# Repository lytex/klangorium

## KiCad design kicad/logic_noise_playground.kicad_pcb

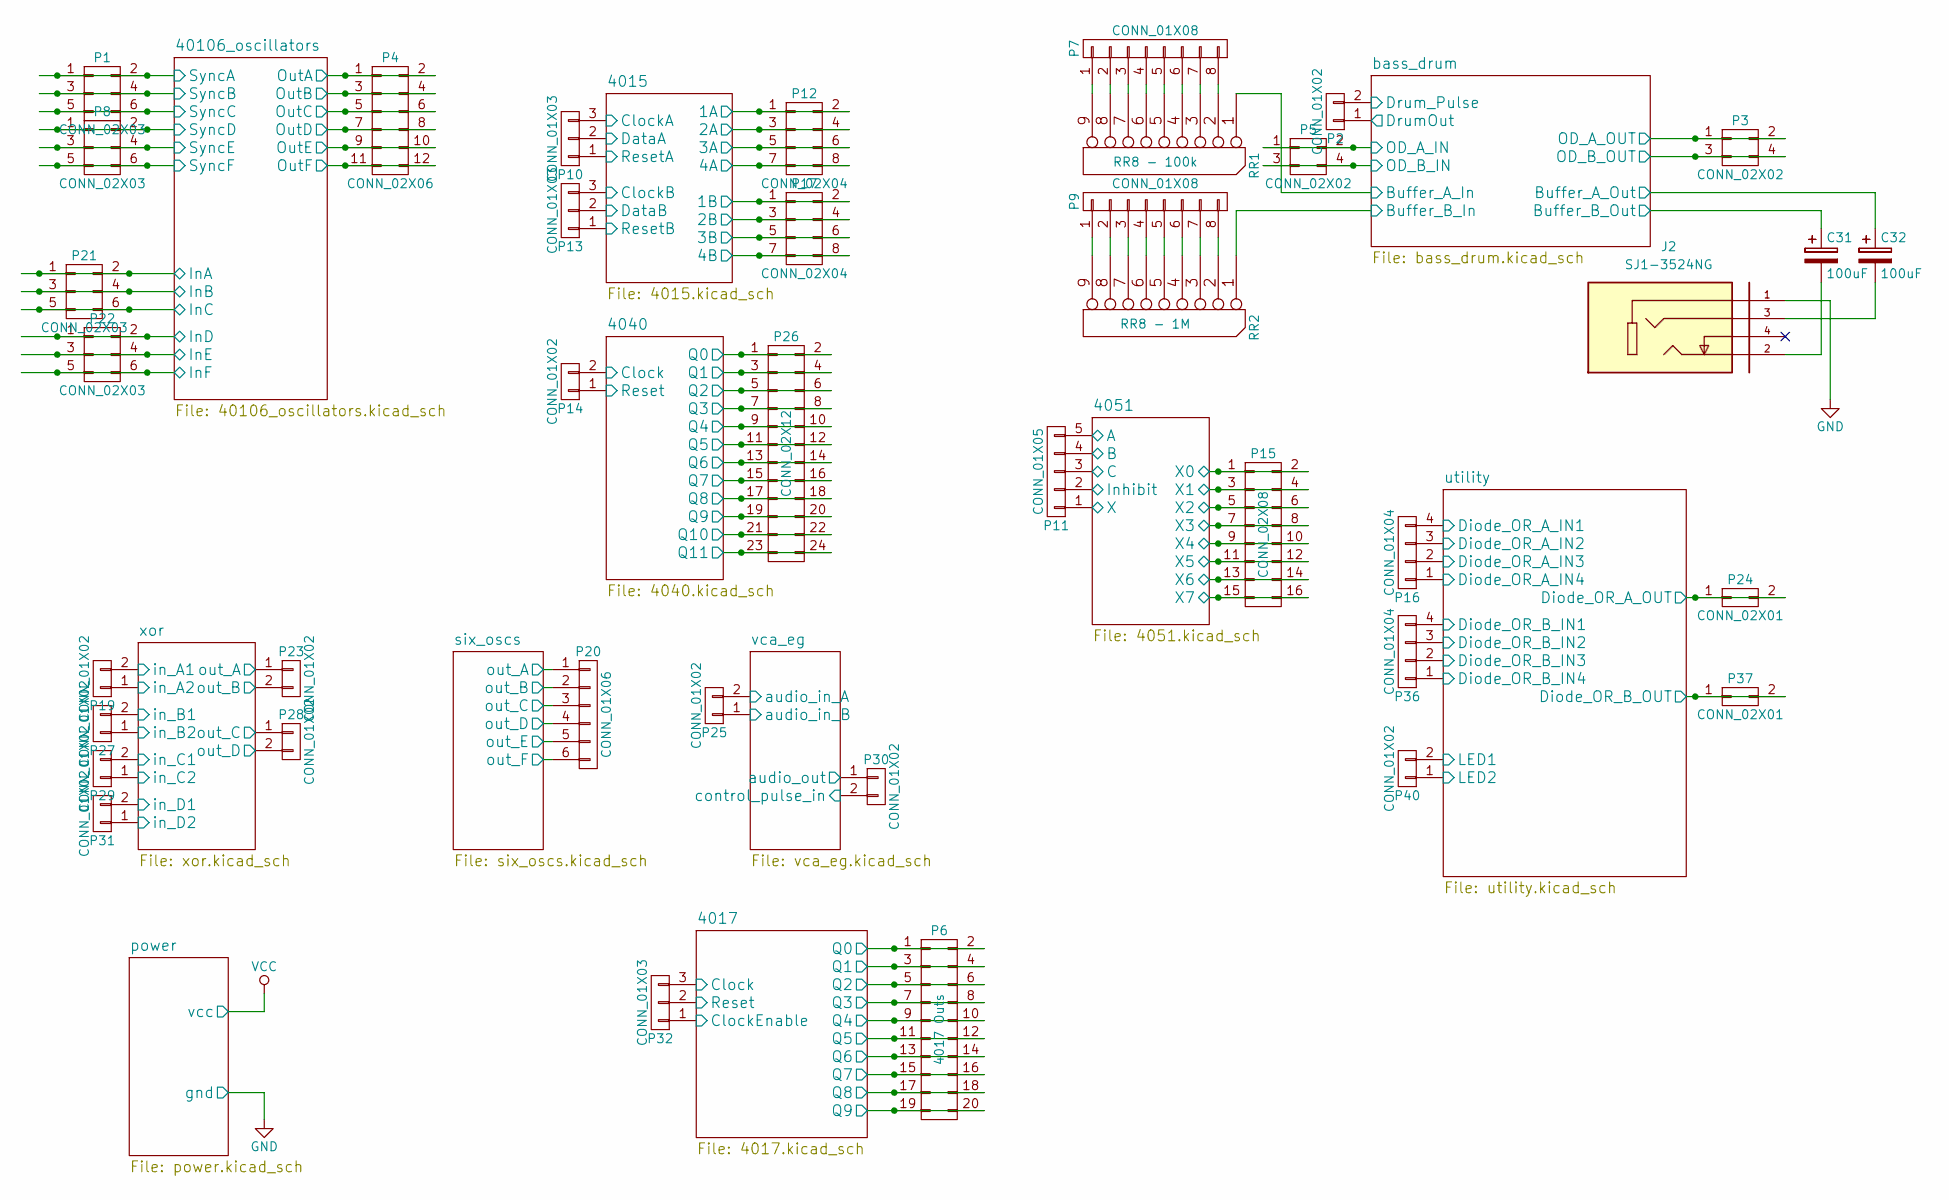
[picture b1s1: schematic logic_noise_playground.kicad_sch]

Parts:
C31, C32: 100uF; Elko_vert_11.2x6.3mm_RM2.5
J2: SJ1-3524NG; CUI_SJ1-3524NG
P1, P8, P21, P22: CONN_02X03; Pin_Header_Straight_2x03
P2, P14, P19, P23, P25, P27, P28, P29, P30, P31, P40: CONN_01X02; Pin_Header_Straight_1x02
P3, P5: CONN_02X02; Pin_Header_Straight_2x02
P4: CONN_02X06; Pin_Header_Straight_2x06
P6: 4017 Outs; Pin_Header_Straight_2x10
P7, P9: CONN_01X08; Pin_Header_Straight_1x08
P10, P13, P32: CONN_01X03; Pin_Header_Straight_1x03
P11: CONN_01X05; Pin_Header_Straight_1x05
P12, P17: CONN_02X04; Pin_Header_Straight_2x04
P15: CONN_02X08; Pin_Header_Straight_2x08
P16, P36: CONN_01X04; Pin_Header_Straight_1x04
P20: CONN_01X06; Pin_Header_Straight_1x06
P24, P37: CONN_02X01; Pin_Header_Straight_2x01
P26: CONN_02X12; Pin_Header_Straight_2x12
RR1: RR8 - 100k; r_pack8
RR2: RR8 - 1M; r_pack8

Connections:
/4015/1A: P12.1, P12.2; also elsewhere on the board
/4015/1B: P17.1, P17.2; also elsewhere on the board
/4015/2A: P12.3, P12.4; also elsewhere on the board
/4015/2B: P17.3, P17.4; also elsewhere on the board
/4015/3A: P12.5, P12.6; also elsewhere on the board
/4015/3B: P17.5, P17.6; also elsewhere on the board
/4015/4A: P12.7, P12.8; also elsewhere on the board
/4015/4B: P17.7, P17.8; also elsewhere on the board
/4015/ClockA: P10.3; also elsewhere on the board
/4015/ClockB: P13.3; also elsewhere on the board
/4015/DataA: P10.2; also elsewhere on the board
/4015/DataB: P13.2; also elsewhere on the board
/4015/ResetA: P10.1; also elsewhere on the board
/4015/ResetB: P13.1; also elsewhere on the board
/4017/Clock: P32.3; also elsewhere on the board
/4017/ClockEnable: P32.1; also elsewhere on the board
/4017/Q0: P6.1, P6.2; also elsewhere on the board
/4017/Q1: P6.3, P6.4; also elsewhere on the board
/4017/Q2: P6.5, P6.6; also elsewhere on the board
/4017/Q3: P6.7, P6.8; also elsewhere on the board
/4017/Q4: P6.9, P6.10; also elsewhere on the board
/4017/Q5: P6.11, P6.12; also elsewhere on the board
/4017/Q6: P6.13, P6.14; also elsewhere on the board
/4017/Q7: P6.15, P6.16; also elsewhere on the board
/4017/Q8: P6.17, P6.18; also elsewhere on the board
/4017/Q9: P6.19, P6.20; also elsewhere on the board
/4017/Reset: P32.2; also elsewhere on the board
/4040/Clock: P14.2; also elsewhere on the board
/4040/Q0: P26.1, P26.2; also elsewhere on the board
/4040/Q1: P26.3, P26.4; also elsewhere on the board
/4040/Q2: P26.5, P26.6; also elsewhere on the board
/4040/Q3: P26.7, P26.8; also elsewhere on the board
/4040/Q4: P26.9, P26.10; also elsewhere on the board
/4040/Q5: P26.11, P26.12; also elsewhere on the board
/4040/Q6: P26.13, P26.14; also elsewhere on the board
/4040/Q7: P26.15, P26.16; also elsewhere on the board
/4040/Q8: P26.17, P26.18; also elsewhere on the board
/4040/Q9: P26.19, P26.20; also elsewhere on the board
/4040/Q10: P26.21, P26.22; also elsewhere on the board
/4040/Q11: P26.23, P26.24; also elsewhere on the board
/4040/Reset: P14.1; also elsewhere on the board
/4051/A: P11.5; also elsewhere on the board
/4051/B: P11.4; also elsewhere on the board
/4051/C: P11.3; also elsewhere on the board
/4051/Inhibit: P11.2; also elsewhere on the board
/4051/X: P11.1; also elsewhere on the board
/4051/X0: P15.1, P15.2; also elsewhere on the board
/4051/X1: P15.3, P15.4; also elsewhere on the board
/4051/X2: P15.5, P15.6; also elsewhere on the board
/4051/X3: P15.7, P15.8; also elsewhere on the board
/4051/X4: P15.9, P15.10; also elsewhere on the board
/4051/X5: P15.11, P15.12; also elsewhere on the board
/4051/X6: P15.13, P15.14; also elsewhere on the board
/4051/X7: P15.15, P15.16; also elsewhere on the board
/40106_oscillators/InA: P21.1, P21.2; also elsewhere on the board
/40106_oscillators/InB: P21.3, P21.4; also elsewhere on the board
/40106_oscillators/InC: P21.5, P21.6; also elsewhere on the board
/40106_oscillators/InD: P22.1, P22.2; also elsewhere on the board
/40106_oscillators/InE: P22.3, P22.4; also elsewhere on the board
/40106_oscillators/InF: P22.5, P22.6; also elsewhere on the board
/40106_oscillators/OutA: P4.1, P4.2; also elsewhere on the board
/40106_oscillators/OutB: P4.3, P4.4; also elsewhere on the board
/40106_oscillators/OutC: P4.5, P4.6; also elsewhere on the board
/40106_oscillators/OutD: P4.7, P4.8; also elsewhere on the board
/40106_oscillators/OutE: P4.9, P4.10; also elsewhere on the board
/40106_oscillators/OutF: P4.11, P4.12; also elsewhere on the board
/40106_oscillators/SyncA: P1.1, P1.2; also elsewhere on the board
/40106_oscillators/SyncB: P1.3, P1.4; also elsewhere on the board
/40106_oscillators/SyncC: P1.5, P1.6; also elsewhere on the board
/40106_oscillators/SyncD: P8.1, P8.2; also elsewhere on the board
/40106_oscillators/SyncE: P8.3, P8.4; also elsewhere on the board
/40106_oscillators/SyncF: P8.5, P8.6; also elsewhere on the board
/bass_drum/Buffer_A_In: RR1.1 (COM); also elsewhere on the board
/bass_drum/Buffer_A_Out: C32.1; also elsewhere on the board
/bass_drum/Buffer_B_In: RR2.1 (COM); also elsewhere on the board
/bass_drum/Buffer_B_Out: C31.1; also elsewhere on the board
/bass_drum/DrumOut: P2.1; also elsewhere on the board
/bass_drum/Drum_Pulse: P2.2; also elsewhere on the board
/bass_drum/OD_A_IN: P5.1, P5.2; also elsewhere on the board
/bass_drum/OD_A_OUT: P3.1, P3.2; also elsewhere on the board
/bass_drum/OD_B_IN: P5.3, P5.4; also elsewhere on the board
/bass_drum/OD_B_OUT: P3.3, P3.4; also elsewhere on the board
/six_oscs/out_A: P20.1; also elsewhere on the board
/six_oscs/out_B: P20.2; also elsewhere on the board
/six_oscs/out_C: P20.3; also elsewhere on the board
/six_oscs/out_D: P20.4; also elsewhere on the board
/six_oscs/out_E: P20.5; also elsewhere on the board
/six_oscs/out_F: P20.6; also elsewhere on the board
/utility/Diode_OR_A_IN1: P16.4; also elsewhere on the board
/utility/Diode_OR_A_IN2: P16.3; also elsewhere on the board
/utility/Diode_OR_A_IN3: P16.2; also elsewhere on the board
/utility/Diode_OR_A_IN4: P16.1; also elsewhere on the board
/utility/Diode_OR_A_OUT: P24.1, P24.2; also elsewhere on the board
/utility/Diode_OR_B_IN1: P36.4; also elsewhere on the board
/utility/Diode_OR_B_IN2: P36.3; also elsewhere on the board
/utility/Diode_OR_B_IN3: P36.2; also elsewhere on the board
/utility/Diode_OR_B_IN4: P36.1; also elsewhere on the board
/utility/Diode_OR_B_OUT: P37.1, P37.2; also elsewhere on the board
/utility/LED1: P40.2; also elsewhere on the board
/utility/LED2: P40.1; also elsewhere on the board
/vca_eg/audio_in_A: P25.2; also elsewhere on the board
/vca_eg/audio_in_B: P25.1; also elsewhere on the board
/vca_eg/audio_out: P30.1; also elsewhere on the board
/vca_eg/control_pulse_in: P30.2; also elsewhere on the board
/xor/in_A1: P19.2; also elsewhere on the board
/xor/in_A2: P19.1; also elsewhere on the board
/xor/in_B1: P27.2; also elsewhere on the board
/xor/in_B2: P27.1; also elsewhere on the board
/xor/in_C1: P29.2; also elsewhere on the board
/xor/in_C2: P29.1; also elsewhere on the board
/xor/in_D1: P31.2; also elsewhere on the board
/xor/in_D2: P31.1; also elsewhere on the board
/xor/out_A: P23.1; also elsewhere on the board
/xor/out_B: P23.2; also elsewhere on the board
/xor/out_C: P28.1; also elsewhere on the board
/xor/out_D: P28.2; also elsewhere on the board
GND: J2.1; also elsewhere on the board
unnamed: C31.2, J2.2
unnamed: C32.2, J2.3
unnamed: P7.1, RR1.9
unnamed: P7.2, RR1.8
unnamed: P7.3, RR1.7
unnamed: P7.4, RR1.6
unnamed: P7.5, RR1.5
unnamed: P7.6, RR1.4
unnamed: P7.7, RR1.3
unnamed: P7.8, RR1.2
unnamed: P9.1, RR2.9
unnamed: P9.2, RR2.8
unnamed: P9.3, RR2.7
unnamed: P9.4, RR2.6
unnamed: P9.5, RR2.5
unnamed: P9.6, RR2.4
unnamed: P9.7, RR2.3
unnamed: P9.8, RR2.2

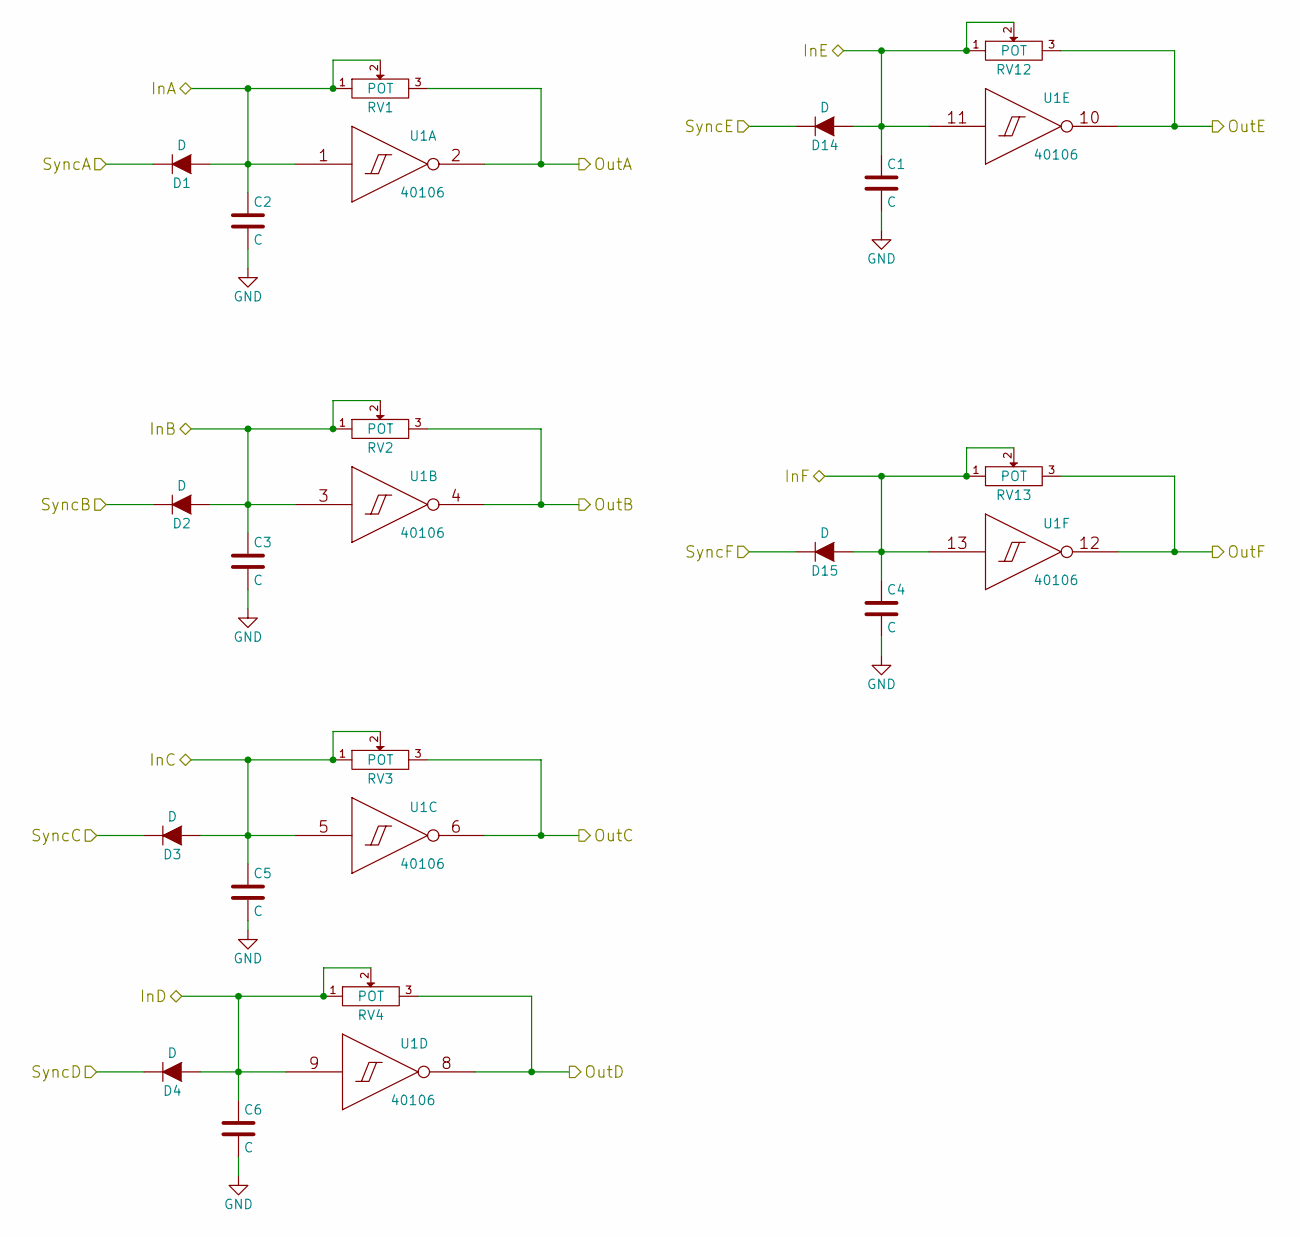
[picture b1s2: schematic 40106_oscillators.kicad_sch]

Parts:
C1, C2, C3, C4, C5, C6: C; cap_2+3
D1, D2, D3, D4, D14, D15: D; Diode_DO-35_SOD27_Horizontal_RM10
RV1, RV2, RV3, RV4, RV12, RV13: POT; PTV09A4025FB104
U1: 40106; DIP-14__300_ELL

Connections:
/40106_oscillators/InA: C2.1, D1.1 (A), RV1.1, RV1.2, U1.1 (In); also elsewhere on the board
/40106_oscillators/InB: C3.1, D2.1 (A), RV2.1, RV2.2, U1.3 (In); also elsewhere on the board
/40106_oscillators/InC: C5.1, D3.1 (A), RV3.1, RV3.2, U1.5 (In); also elsewhere on the board
/40106_oscillators/InD: C6.1, D4.1 (A), RV4.1, RV4.2, U1.9 (In); also elsewhere on the board
/40106_oscillators/InE: C1.1, D14.1 (A), RV12.1, RV12.2, U1.11 (In); also elsewhere on the board
/40106_oscillators/InF: C4.1, D15.1 (A), RV13.1, RV13.2, U1.13 (In); also elsewhere on the board
/40106_oscillators/OutA: RV1.3, U1.2 (Out); also elsewhere on the board
/40106_oscillators/OutB: RV2.3, U1.4 (Out); also elsewhere on the board
/40106_oscillators/OutC: RV3.3, U1.6 (Out); also elsewhere on the board
/40106_oscillators/OutD: RV4.3, U1.8 (Out); also elsewhere on the board
/40106_oscillators/OutE: RV12.3, U1.10 (Out); also elsewhere on the board
/40106_oscillators/OutF: RV13.3, U1.12 (Out); also elsewhere on the board
/40106_oscillators/SyncA: D1.2 (K); also elsewhere on the board
/40106_oscillators/SyncB: D2.2 (K); also elsewhere on the board
/40106_oscillators/SyncC: D3.2 (K); also elsewhere on the board
/40106_oscillators/SyncD: D4.2 (K); also elsewhere on the board
/40106_oscillators/SyncE: D14.2 (K); also elsewhere on the board
/40106_oscillators/SyncF: D15.2 (K); also elsewhere on the board
GND: C1.2, C2.2, C3.2, C4.2, C5.2, C6.2, U1.7 (VSS); also elsewhere on the board
VCC: U1.14 (VDD); also elsewhere on the board

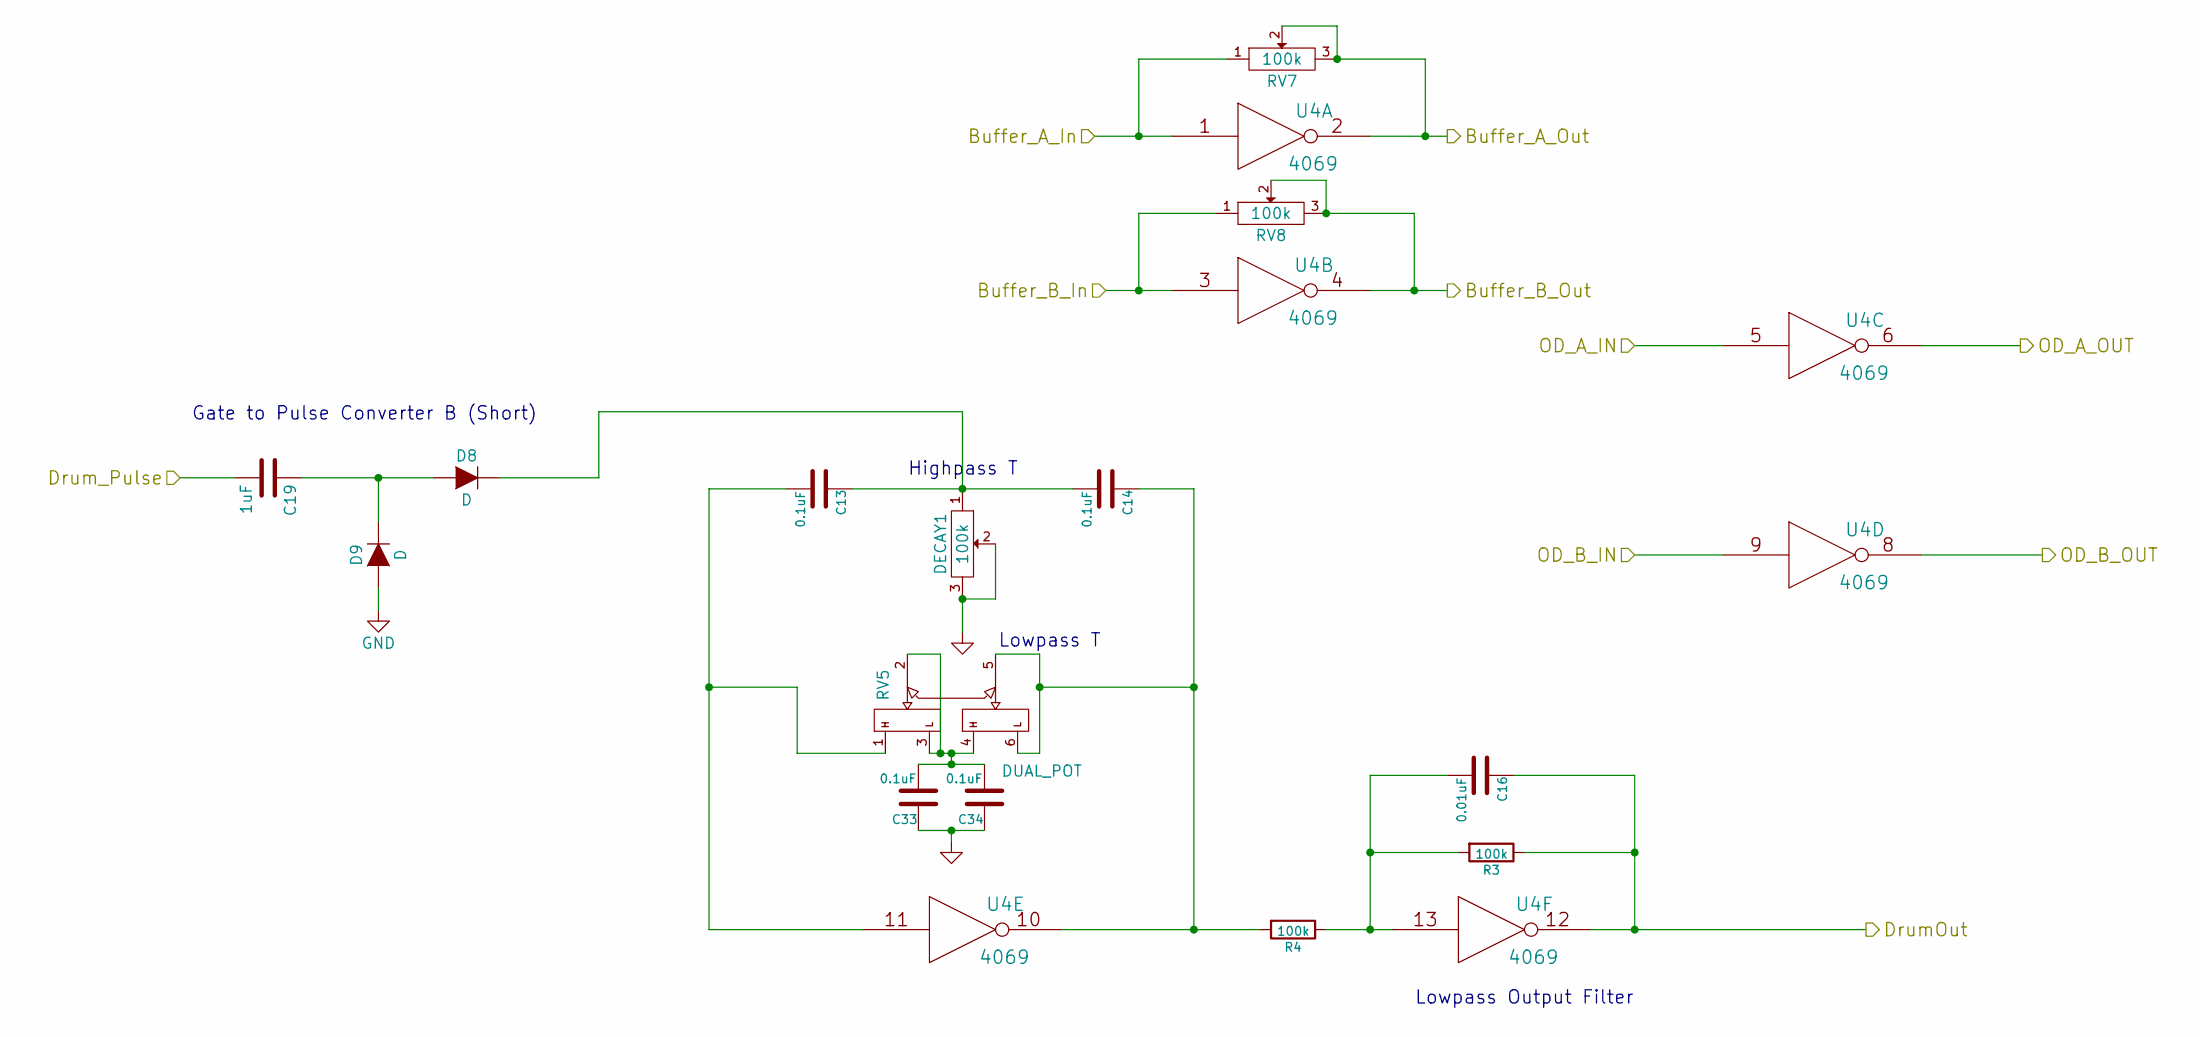
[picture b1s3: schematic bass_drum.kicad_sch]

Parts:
C13, C14, C33, C34: 0.1uF; C1
C16: 0.01uF; C1
C19: 1uF; C1
D8, D9: D; Diode_DO-35_SOD27_Horizontal_RM10
DECAY1: 100k; PTV09A4025FB104
R3, R4: 100k; Resistor_Horizontal_RM10mm
RV5: DUAL_POT; Potentiometer_Alps_RK163_Dual_Horizontal
RV7, RV8: 100k; PTV09A4025FB104
U4: 4069; DIP-14__300_ELL

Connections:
/bass_drum/Buffer_A_In: RV7.1, U4.1; also elsewhere on the board
/bass_drum/Buffer_A_Out: RV7.2, RV7.3, U4.2; also elsewhere on the board
/bass_drum/Buffer_B_In: RV8.1, U4.3; also elsewhere on the board
/bass_drum/Buffer_B_Out: RV8.2, RV8.3, U4.4; also elsewhere on the board
/bass_drum/DrumOut: C16.1, R3.1, U4.12; also elsewhere on the board
/bass_drum/Drum_Pulse: C19.2; also elsewhere on the board
/bass_drum/OD_A_IN: U4.5; also elsewhere on the board
/bass_drum/OD_A_OUT: U4.6; also elsewhere on the board
/bass_drum/OD_B_IN: U4.9; also elsewhere on the board
/bass_drum/OD_B_OUT: U4.8; also elsewhere on the board
GND: C33.1, C34.1, D9.1 (A), DECAY1.2, DECAY1.3, U4.7 (VSS); also elsewhere on the board
unnamed: C13.2, RV5.1, U4.11
unnamed: C14.1, R4.2, RV5.5, RV5.6, U4.10
unnamed: C16.2, R3.2, R4.1, U4.13
unnamed: C33.2, C34.2, RV5.2, RV5.3, RV5.4
unnamed: C19.1, D8.1 (A), D9.2 (K)
unnamed: C13.1, C14.2, D8.2 (K), DECAY1.1
VCC: U4.14 (VDD); also elsewhere on the board

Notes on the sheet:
Highpass T
Lowpass Output Filter
Gate to Pulse Converter B (Short)
Lowpass T

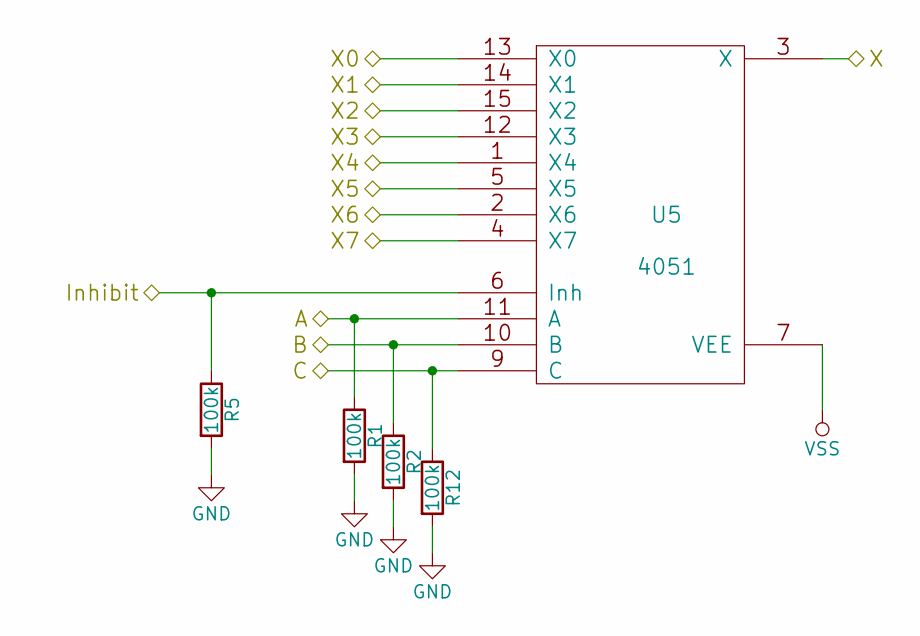
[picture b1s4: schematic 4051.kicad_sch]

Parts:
R1, R2, R5, R12: 100k; Resistor_Horizontal_RM10mm
U5: 4051; DIP-16__300_ELL

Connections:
/4051/A: R1.1, U5.11 (A); also elsewhere on the board
/4051/B: R2.1, U5.10 (B); also elsewhere on the board
/4051/C: R12.1, U5.9 (C); also elsewhere on the board
/4051/Inhibit: R5.1, U5.6 (Inh); also elsewhere on the board
/4051/X: U5.3 (X); also elsewhere on the board
/4051/X0: U5.13 (X0); also elsewhere on the board
/4051/X1: U5.14 (X1); also elsewhere on the board
/4051/X2: U5.15 (X2); also elsewhere on the board
/4051/X3: U5.12 (X3); also elsewhere on the board
/4051/X4: U5.1 (X4); also elsewhere on the board
/4051/X5: U5.5 (X5); also elsewhere on the board
/4051/X6: U5.2 (X6); also elsewhere on the board
/4051/X7: U5.4 (X7); also elsewhere on the board
GND: R1.2, R2.2, R5.2, R12.2, U5.7 (VEE), U5.8 (VSS); also elsewhere on the board
VCC: U5.16 (VDD); also elsewhere on the board

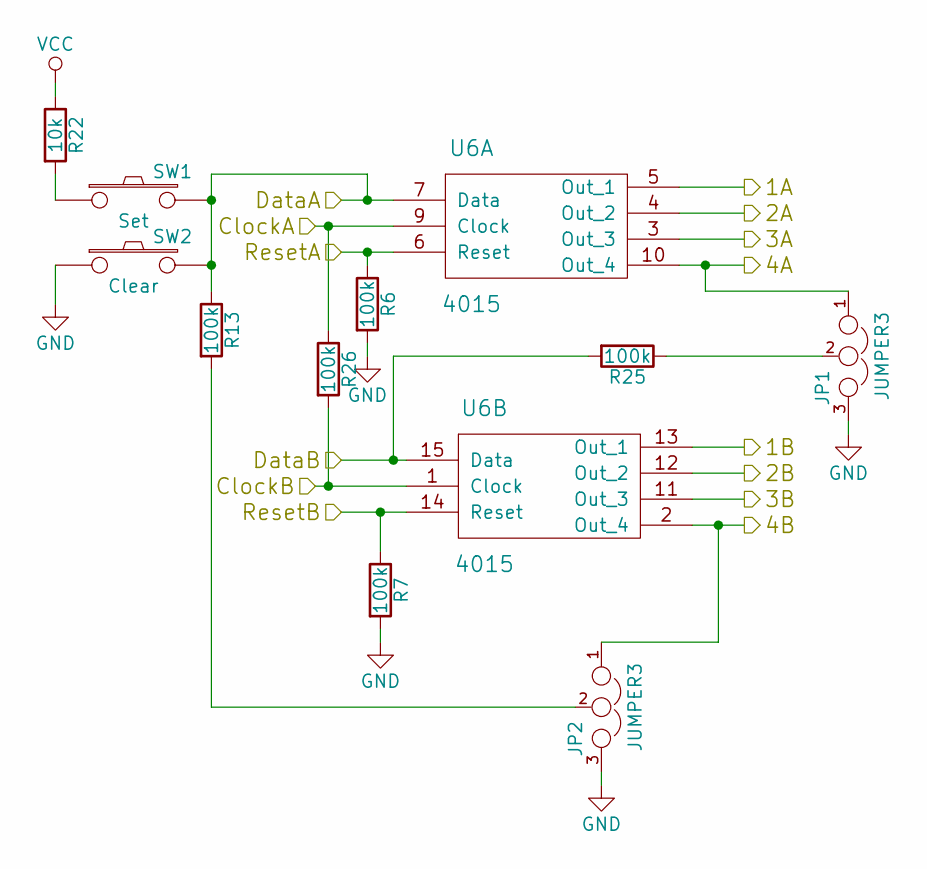
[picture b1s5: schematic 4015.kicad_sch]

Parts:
JP1, JP2: JUMPER3; Socket_Strip_Straight_1x03
R6, R7, R13, R25, R26: 100k; Resistor_Horizontal_RM10mm
R22: 10k; Resistor_Horizontal_RM10mm
SW1: Set; SW_PUSH_SMALL
SW2: Clear; SW_PUSH_SMALL
U6: 4015; DIP-16__300_ELL

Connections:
/4015/1A: U6.5 (Out_1); also elsewhere on the board
/4015/1B: U6.13 (Out_1); also elsewhere on the board
/4015/2A: U6.4 (Out_2); also elsewhere on the board
/4015/2B: U6.12 (Out_2); also elsewhere on the board
/4015/3A: U6.3 (Out_3); also elsewhere on the board
/4015/3B: U6.11 (Out_3); also elsewhere on the board
/4015/4A: JP1.1, U6.10 (Out_4); also elsewhere on the board
/4015/4B: JP2.1, U6.2 (Out_4); also elsewhere on the board
/4015/ClockA: R26.1, U6.9 (Clock); also elsewhere on the board
/4015/ClockB: R26.2, U6.1 (Clock); also elsewhere on the board
/4015/DataA: R13.1, SW1.2, SW2.2, U6.7 (Data); also elsewhere on the board
/4015/DataB: R25.2, U6.15 (Data); also elsewhere on the board
/4015/ResetA: R6.1, U6.6 (Reset); also elsewhere on the board
/4015/ResetB: R7.1, U6.14 (Reset); also elsewhere on the board
GND: JP1.3, JP2.3, R6.2, R7.2, SW2.1, U6.8 (VSS); also elsewhere on the board
unnamed: JP1.2, R25.1
unnamed: JP2.2, R13.2
unnamed: R22.2, SW1.1
VCC: R22.1, U6.16 (VDD); also elsewhere on the board

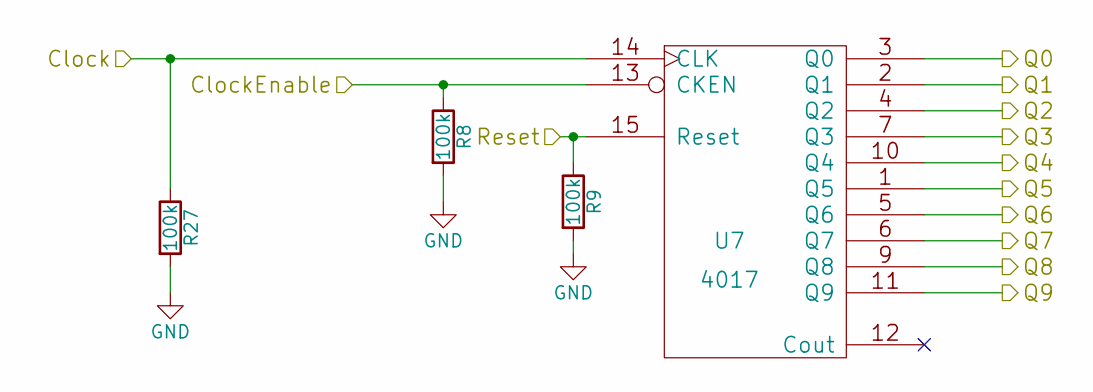
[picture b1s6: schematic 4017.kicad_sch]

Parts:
R8, R9, R27: 100k; Resistor_Horizontal_RM10mm
U7: 4017; DIP-16__300_ELL

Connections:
/4017/Clock: R27.1, U7.14 (CLK); also elsewhere on the board
/4017/ClockEnable: R8.1, U7.13 (CKEN); also elsewhere on the board
/4017/Q0: U7.3 (Q0); also elsewhere on the board
/4017/Q1: U7.2 (Q1); also elsewhere on the board
/4017/Q2: U7.4 (Q2); also elsewhere on the board
/4017/Q3: U7.7 (Q3); also elsewhere on the board
/4017/Q4: U7.10 (Q4); also elsewhere on the board
/4017/Q5: U7.1 (Q5); also elsewhere on the board
/4017/Q6: U7.5 (Q6); also elsewhere on the board
/4017/Q7: U7.6 (Q7); also elsewhere on the board
/4017/Q8: U7.9 (Q8); also elsewhere on the board
/4017/Q9: U7.11 (Q9); also elsewhere on the board
/4017/Reset: R9.1, U7.15 (Reset); also elsewhere on the board
GND: R8.2, R9.2, R27.2, U7.8 (VSS); also elsewhere on the board
VCC: U7.16 (VDD); also elsewhere on the board

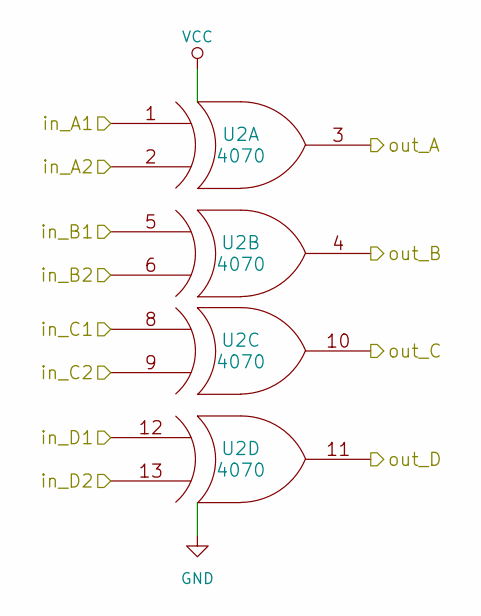
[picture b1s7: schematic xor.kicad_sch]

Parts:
U2: 4070; DIP-14__300_ELL

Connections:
/xor/in_A1: U2.1; also elsewhere on the board
/xor/in_A2: U2.2; also elsewhere on the board
/xor/in_B1: U2.5; also elsewhere on the board
/xor/in_B2: U2.6; also elsewhere on the board
/xor/in_C1: U2.8; also elsewhere on the board
/xor/in_C2: U2.9; also elsewhere on the board
/xor/in_D1: U2.12; also elsewhere on the board
/xor/in_D2: U2.13; also elsewhere on the board
/xor/out_A: U2.3; also elsewhere on the board
/xor/out_B: U2.4; also elsewhere on the board
/xor/out_C: U2.10; also elsewhere on the board
/xor/out_D: U2.11; also elsewhere on the board
GND: U2.7 (VSS); also elsewhere on the board
VCC: U2.14 (VDD); also elsewhere on the board

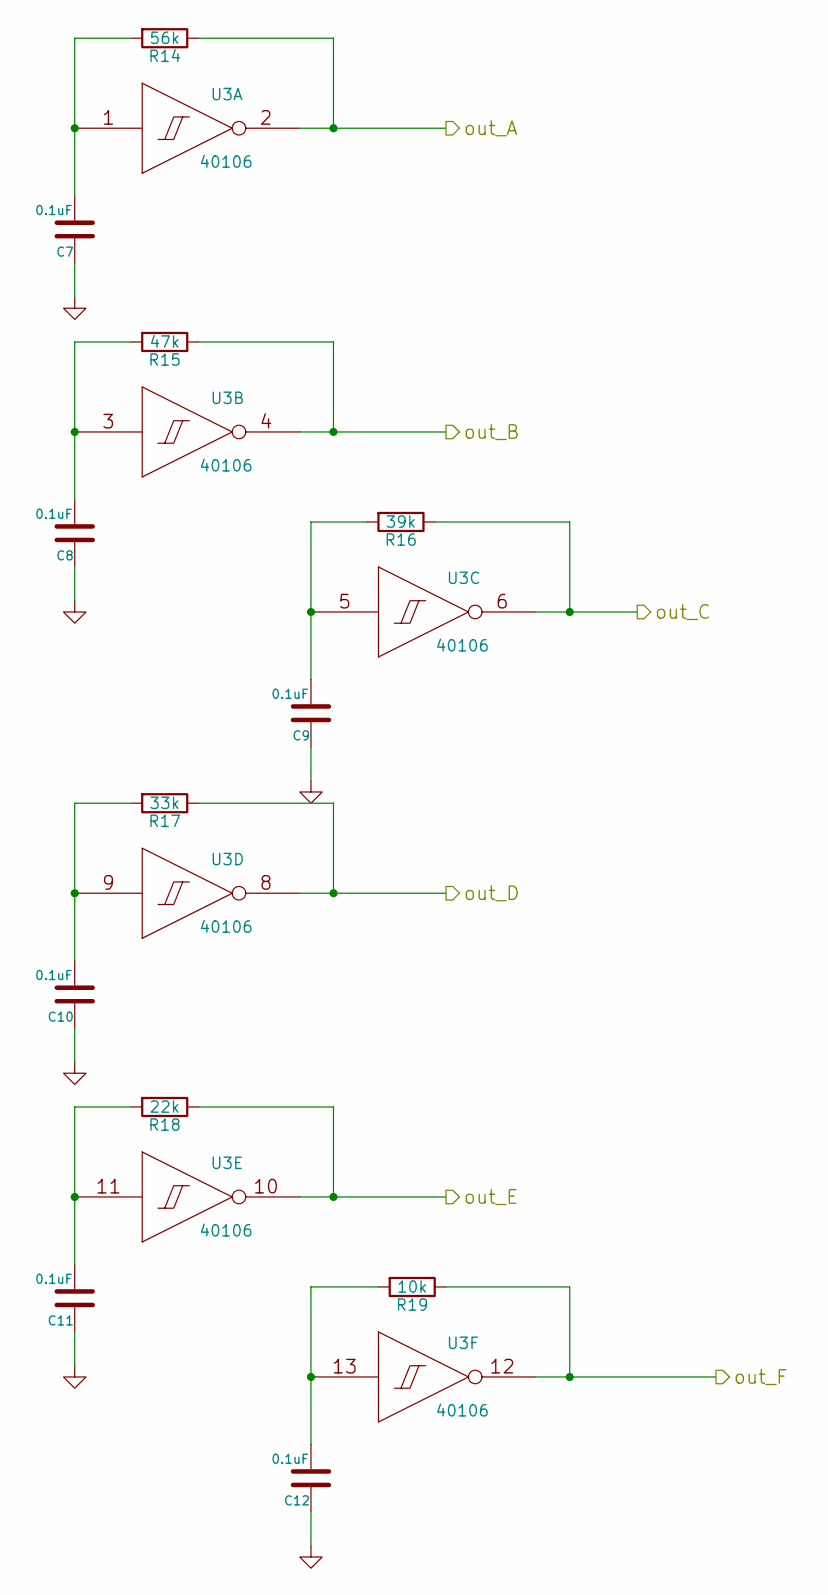
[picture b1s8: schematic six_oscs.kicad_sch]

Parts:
C7, C8, C9, C10, C11, C12: 0.1uF; C1
R14: 56k; Resistor_Horizontal_RM10mm
R15: 47k; Resistor_Horizontal_RM10mm
R16: 39k; Resistor_Horizontal_RM10mm
R17: 33k; Resistor_Horizontal_RM10mm
R18: 22k; Resistor_Horizontal_RM10mm
R19: 10k; Resistor_Horizontal_RM10mm
U3: 40106; DIP-14__300_ELL

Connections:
/six_oscs/out_A: R14.1, U3.2 (Out); also elsewhere on the board
/six_oscs/out_B: R15.1, U3.4 (Out); also elsewhere on the board
/six_oscs/out_C: R16.1, U3.6 (Out); also elsewhere on the board
/six_oscs/out_D: R17.1, U3.8 (Out); also elsewhere on the board
/six_oscs/out_E: R18.1, U3.10 (Out); also elsewhere on the board
/six_oscs/out_F: R19.1, U3.12 (Out); also elsewhere on the board
GND: C7.1, C8.1, C9.1, C10.1, C11.1, C12.1, U3.7 (VSS); also elsewhere on the board
unnamed: C7.2, R14.2, U3.1 (In)
unnamed: C8.2, R15.2, U3.3 (In)
unnamed: C9.2, R16.2, U3.5 (In)
unnamed: C10.2, R17.2, U3.9 (In)
unnamed: C11.2, R18.2, U3.11 (In)
unnamed: C12.2, R19.2, U3.13 (In)
VCC: U3.14 (VDD); also elsewhere on the board

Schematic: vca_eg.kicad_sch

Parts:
C15: 1uF; C1
C21, C22: 10uF; Elko_vert_11.2x6.3mm_RM2.5
D12, D13, D16, D17: D; Diode_DO-35_SOD27_Horizontal_RM10
Q1: LM3904; TO92
R20, R21: 100k; Resistor_Horizontal_RM10mm
R23: 10K; Resistor_Horizontal_RM10mm
R24: 1k; Resistor_Horizontal_RM10mm
RV6: POT; PTV09A4025FB104

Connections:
/vca_eg/audio_in_A: R20.1; also elsewhere on the board
/vca_eg/audio_in_B: R21.2; also elsewhere on the board
/vca_eg/audio_out: C15.1; also elsewhere on the board
/vca_eg/control_pulse_in: C21.1; also elsewhere on the board
GND: C22.2, D17.1 (A), R24.2, RV6.2, RV6.3; also elsewhere on the board
unnamed: D12.1 (A), D13.1 (A), R23.1
unnamed: D12.2 (K), R20.2, R21.1
unnamed: D13.2 (K), Q1.2 (B)
unnamed: C21.2, D16.1 (A), D17.2 (K)
unnamed: C22.1, D16.2 (K), R23.2, RV6.1
unnamed: C15.2, Q1.3 (E), R24.1
VCC: Q1.1 (C); also elsewhere on the board

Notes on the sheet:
pol caps
VCA_A
Gate to Pulse Converter A (Long)

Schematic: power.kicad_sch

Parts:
C20: 10uF; Elko_vert_11.2x6.3mm_RM2.5
C23, C24, C25, C26, C27, C28, C29, C30: 0.1uF; C1
CONN1: ss_3_header; connector_ss_3pin

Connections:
GND: C20.2, C23.2, C24.2, C25.2, C26.2, C27.2, C28.2, C29.2, C30.2, CONN1.1 (GND); also elsewhere on the board
VCC: C20.1, C23.1, C24.1, C25.1, C26.1, C27.1, C28.1, C29.1, C30.1, CONN1.2 (VCC); also elsewhere on the board

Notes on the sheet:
Locate near each chip

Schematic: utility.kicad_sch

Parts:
D5, D6, D7, D10, D11, D18, D19, D20: D; Diode_DO-35_SOD27_Horizontal_RM10
D21, D22: LED; LED-5MM
P18, P33, P34, P35, P38, P39: CONN_01X04; Pin_Header_Straight_1x04
R10, R28: 100K; Resistor_Horizontal_RM10mm
R29, R30: 1k; Resistor_Horizontal_RM10mm

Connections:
/utility/Diode_OR_A_IN1: D5.1 (A); also elsewhere on the board
/utility/Diode_OR_A_IN2: D6.1 (A); also elsewhere on the board
/utility/Diode_OR_A_IN3: D7.1 (A); also elsewhere on the board
/utility/Diode_OR_A_IN4: D10.1 (A); also elsewhere on the board
/utility/Diode_OR_A_OUT: D5.2 (K), D6.2 (K), D7.2 (K), D10.2 (K), R10.1; also elsewhere on the board
/utility/Diode_OR_B_IN1: D11.1 (A); also elsewhere on the board
/utility/Diode_OR_B_IN2: D18.1 (A); also elsewhere on the board
/utility/Diode_OR_B_IN3: D19.1 (A); also elsewhere on the board
/utility/Diode_OR_B_IN4: D20.1 (A); also elsewhere on the board
/utility/Diode_OR_B_OUT: D11.2 (K), D18.2 (K), D19.2 (K), D20.2 (K), R28.1; also elsewhere on the board
/utility/LED1: D21.1 (A); also elsewhere on the board
/utility/LED2: D22.1 (A); also elsewhere on the board
GND: P39.1, P39.2, P39.3, P39.4, R10.2, R28.2, R29.2, R30.2; also elsewhere on the board
unnamed: D21.2 (K), R29.1
unnamed: D22.2 (K), R30.1
unnamed: P18.1, P18.2, P18.3, P18.4
unnamed: P33.1, P33.2, P33.3, P33.4
unnamed: P34.1, P34.2, P34.3, P34.4
unnamed: P35.1, P35.2, P35.3, P35.4
VCC: P38.1, P38.2, P38.3, P38.4; also elsewhere on the board

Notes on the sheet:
Diode OR

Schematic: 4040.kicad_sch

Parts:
R11: 100k; Resistor_Horizontal_RM10mm
U8: 4040; DIP-16__300_ELL

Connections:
/4040/Clock: U8.10 (CLK); also elsewhere on the board
/4040/Q0: U8.9 (Q0); also elsewhere on the board
/4040/Q1: U8.7 (Q1); also elsewhere on the board
/4040/Q2: U8.6 (Q2); also elsewhere on the board
/4040/Q3: U8.5 (Q3); also elsewhere on the board
/4040/Q4: U8.3 (Q4); also elsewhere on the board
/4040/Q5: U8.2 (Q5); also elsewhere on the board
/4040/Q6: U8.4 (Q6); also elsewhere on the board
/4040/Q7: U8.13 (Q7); also elsewhere on the board
/4040/Q8: U8.12 (Q8); also elsewhere on the board
/4040/Q9: U8.14 (Q9); also elsewhere on the board
/4040/Q10: U8.15 (Q10); also elsewhere on the board
/4040/Q11: U8.1 (Q11); also elsewhere on the board
/4040/Reset: R11.1, U8.11 (Reset); also elsewhere on the board
GND: R11.2, U8.8 (VSS); also elsewhere on the board
VCC: U8.16 (VDD); also elsewhere on the board

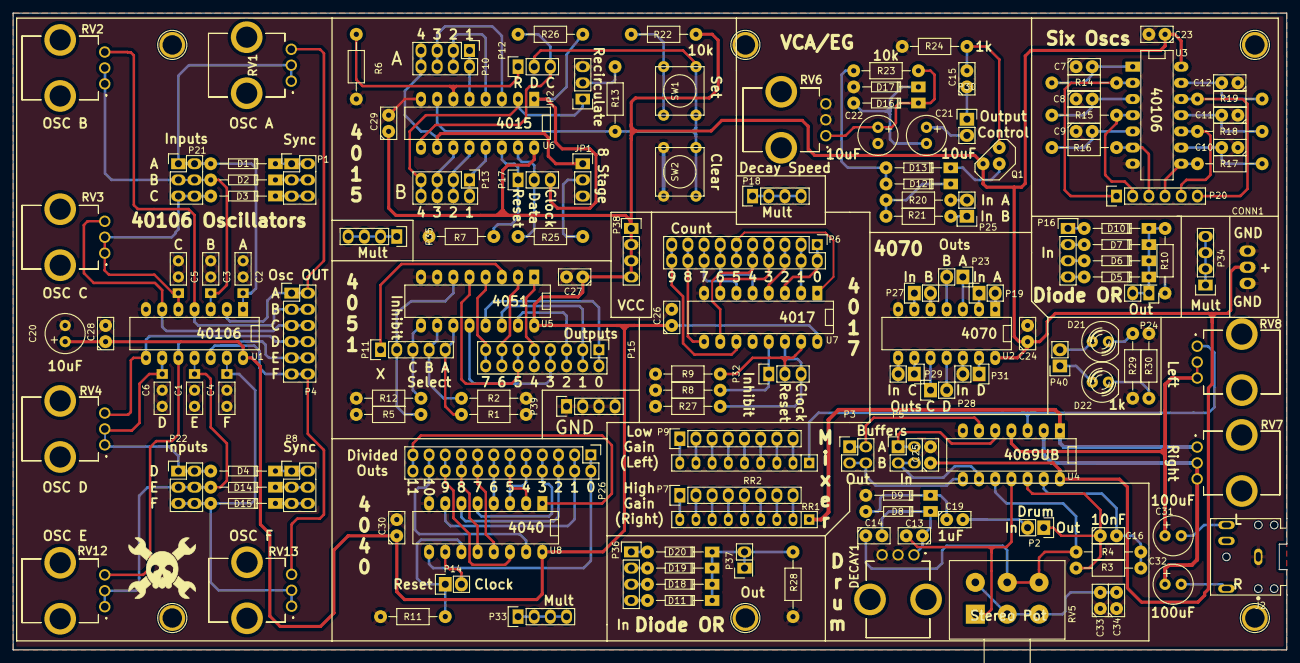
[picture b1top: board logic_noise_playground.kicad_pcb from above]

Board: 2 copper layers, 200.0 x 100.0 mm, 152 parts (0 on the bottom side), 163 nets.

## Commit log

2024-02-27 Saved from KiCad 8.0 and parts list information
2024-03-22 update all project to KiCad8
2024-03-22 erase previous files
2024-03-22 fix silkscreen labels
2024-03-22 fix vcc and grounding
2024-03-22 update part numbers
2024-03-22 update traces
2024-03-27 add gitignore lck files
2024-03-27 change pots
2024-03-27 update resistors values
2024-03-28 update connectors
2024-04-01 update caps
2024-04-01 update stereo TRSS connector
2024-06-03 update BOM
2024-08-13 update reference number output
2024-08-22 update gerbers
2025-04-21 update to kicad 9, add some comments and circuit changes
